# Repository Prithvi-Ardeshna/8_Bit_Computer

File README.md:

# 8-Bit Computer 

This project is a simulation of an 8-bit computer built using [Logisim Evolution](https://github.com/reds-heig/logisim-evolution), inspired by [Ben Eater's YouTube series](https://www.youtube.com/playlist?list=PLowKtXNTBypGqImE405J2565dvjafglHU).  
It demonstrates the basic architecture and functioning of a simple CPU, including a version with full control logic and basic instruction set support.

---

## Project Overview

This project includes **two versions** of the 8-bit CPU:

1. **Basic Version (without control logic):**  
   - Manually controlled CPU execution by execution micro instructions at a time.
   - Useful for learning how individual components interact.

2. **Full Version (with control logic):**  
   - Automated instruction execution using a control logic ROM.
   - Supports a simple assembly-like instruction set.

---

## Features

- Simulates an 8-bit CPU architecture.
- Includes ALU, Registers, RAM, Memory Address Register, Program Counter, Instruction Register, Flag Register, Control Logic, and Output Register.
- Simple instruction set to write and execute custom programs.
- C program to generate microcode that has to be loaded in control logic rom.

---

## Components

   **Clock**               

   **Program Counter**

   **A Register**        

   **B Register**     

   **ALU**             

   **Output Register**                       

   **Memory Address Register**               

   **RAM**                      

   **Instruction Register**         

   **Step Counter**                    

   **Zero Flag**                    

   **Flags**                         

---

## Instruction Set

| Opcode | Mnemonic | Description                     |
|--------|----------|---------------------------------|
| `0000` | NOP      | No operation                    |
| `0001` | LDA      | Load from RAM to A              |
| `0010` | ADD      | Add value to A                  |
| `0011` | SUB      | Subtract value from A           |
| `0100` | STA      | Store A to RAM                  |
| `0101` | LDI      | Load A with given value         |
| `0110` | JMP      | Jump to address                 |
| `0111` | JC       | Jump if carry flag is set       |
| `1000` | JZ       | Jump if zero flag is set        |
| `1110` | OUT      | Load from A to output register  |
| `1111` | HLT      | Halt execution                  |

---

## Examples

1) Using basic version to add two numbers

   Program:
   | Assembly | Memory Address | Machine Code |
   |----------|----------------|--------------|
   | LDA 14   | `0000`         | `0001 1110`  |
   | ADD 15   | `0001`         | `0010 1111`  |
   | OUT      | `0010`         | `1110 0000`  |
   |          |  ...           |              |
   |          | `1110`         | `0001 1100`  |
   |          | `1111`         | `0000 1110`  |

   Micro Instructions:

   |    | LDA 14 |                                                   | 
   |----|--------|---------------------------------------------------|
   | T0 | CO MI  | Going to Memory Address '0000' (Fetch opertation) |
   | T1 | RO II  | Transfer Data from RAM To IR                      |
   |    | CE     | Increment PC                                      |
   | T2 | IO MI  | Pointing Memory at address '1110'                 |
   | T3 | RO AI  | Store data in A                                   |

   |    | ADD 15 |                                                   | 
   |----|--------|---------------------------------------------------|
   | T0 | CO MI  | Going to Memory Address '0001' (Fetch opertation) |
   | T1 | RO II  | Transfer Data from RAM To IR                      |
   |    | CE     | Increment PC                                      |
   | T2 | IO MI  | Pointing Memory at address '1111'                 |
   | T3 | RO BI  | Store data in B                                   |
   | T4 | EO AI  | Calculate sum of A and B and store it in A        |

   |    | OUT    |                                                                  |
   |----|--------|------------------------------------------------------------------|
   | T0 | CO MI  | Going to Memory Address '0010' (Fetch opertation)                |
   | T1 | RO II  | Transfer Data from RAM To IR                                     |
   |    | CE     | Increment PC                                                     |
   | T2 | AO OI  | data stored in A is transfered to Output Register for displaying |

2) Getting Multiples of 3
   
   Program:
   | Assembly  | Memory Address | Machine Code |
   |-----------|----------------|--------------|
   | 0: LDI 03 | `0000`         | `0101 0011`  |
   | 1: STA 15 | `0001`         | `0100 1111`  |
   | 2: LDI 00 | `0010`         | `0101 0000`  |
   | 3: ADD 15 | `0011`         | `0010 1111`  |
   | 4: OUT    | `0100`         | `1110 0000`  |
   | 5: JMP 03 | `0101`         | `0110 0011`  |

3) Counting Up and Down

   Program:
   | Assembly   | Memory Address | Machine Code |
   |------------|----------------|--------------|
   | 00: OUT    | `0000`         | `1110 0000`  |
   | 01: ADD 15 | `0001`         | `0010 1111`  |
   | 02: JC 04  | `0010`         | `0111 0100`  |
   | 03: JMP 00 | `0011`         | `0110 0000`  |
   | 04: SUB 15 | `0100`         | `0011 1111`  |
   | 05: OUT    | `0101`         | `111O OOOO`  |
   | 06: JZ 00  | `0110`         | `1000 0000`  |
   | 07: JMP 04 | `0111`         | `0110 0100`  |
   | 15: 25     | `1111`         | `0011 0010`  |

4) Multipling x & y using conditional jump

   Pseudocode:\
   product = 0\
   loop until x is 0\
   &emsp;load x\
   &emsp;subtract 1\
   &emsp;store x\
   &emsp;load product\
   &emsp;add y\
   &emsp;store product\
   output product

   Assembly:\
   TOP:\
   &emsp;LDA x\
   &emsp;SUB 1\
   &emsp;JC CONTINUE\
   &emsp;LDA product\
   &emsp;OUT\
   &emsp;HLT\
   CONTINUE:\
   &emsp;STA x\
   &emsp;LDA product\
   &emsp;ADD y\
   &emsp;STA product\
   &emsp;JMP TOP

   Program:
   | Assembly    | Memory Address | Machine Code |
   |-------------|----------------|--------------|
   | 00: LDA 14  | `0000`         | `0001 1110`  |
   | 01: SUB 12  | `0001`         | `0011 1100`  |
   | 02: JC 06   | `0010`         | `0111 0110`  |
   | 03: LDA 13  | `0011`         | `0001 1101`  |
   | 04: OUT     | `0100`         | `1110 0000`  |
   | 05: HLT     | `0101`         | `1111 0000`  |
   | 06: STA 14  | `0110`         | `0100 1110`  |
   | 07: LDA 13  | `0111`         | `0001 1101`  |
   | 08: ADD 15  | `1000`         | `0010 1111`  |
   | 09: STA 13  | `1001`         | `0100 1101`  |
   | 10: JMP 00  | `1010`         | `0110 0000`  |
   | 11:         | `1011`         |              |
   | 12: 1       | `1100`         | `0000 0001`  |
   | 13: product | `1101`         | `0000 0000`  |
   | 14: x       | `1110`         |              |
   | 15: y       | `1111`         |              |

---

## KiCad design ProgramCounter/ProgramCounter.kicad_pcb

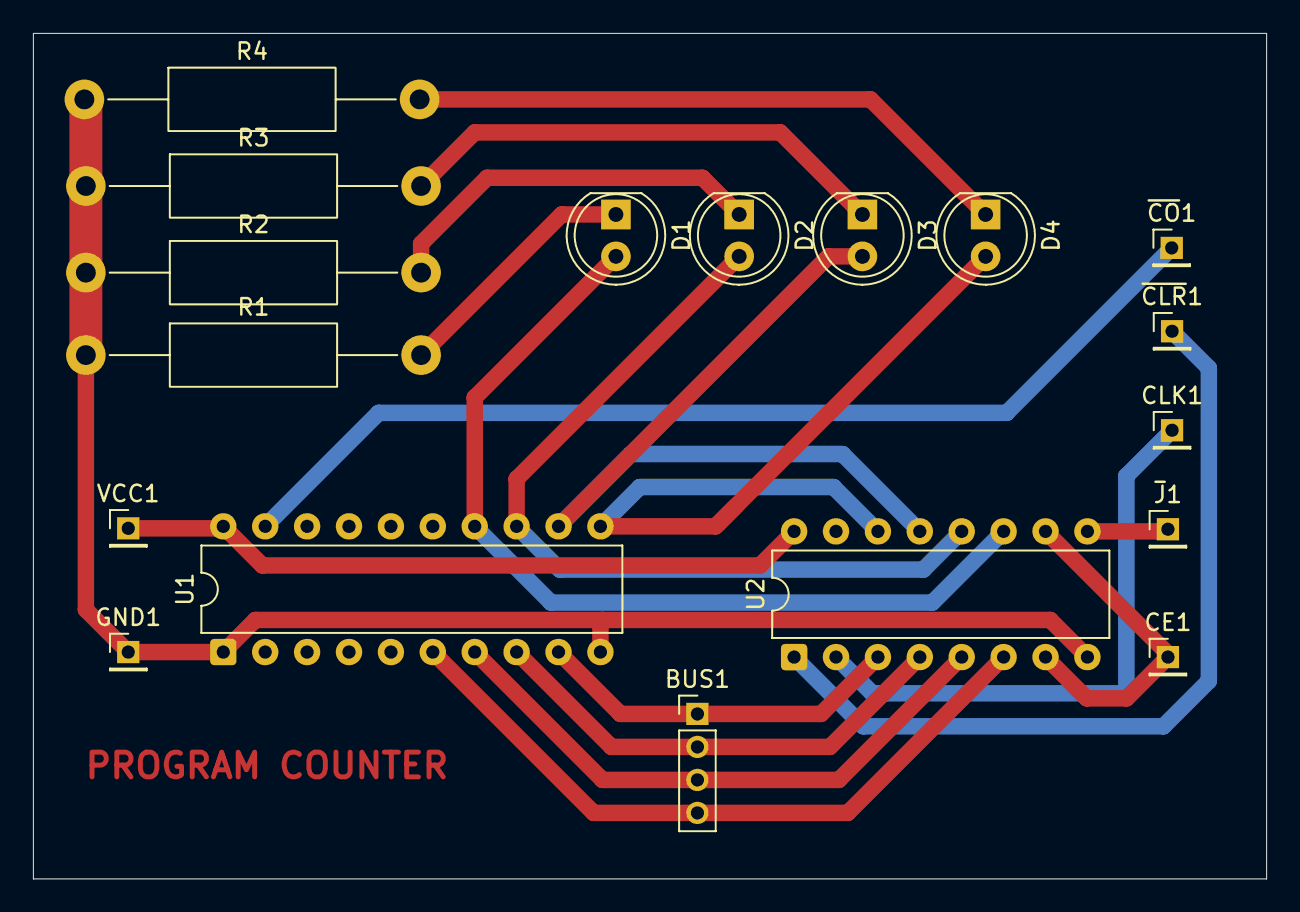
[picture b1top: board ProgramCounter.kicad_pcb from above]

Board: 2 copper layers, 74.8 x 51.2 mm, 15 parts (0 on the bottom side), 16 nets.

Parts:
BUS1: Conn_01x04_Pin; PinHeader_1x04_P2.00mm_Vertical
CE1: Conn_01x01_Pin; PinHeader_1x01_P2.00mm_Vertical
CLK1: Conn_01x01_Pin; PinHeader_1x01_P2.00mm_Vertical
D1, D2, D3, D4: LED; LED_D5.0mm
GND1: Conn_01x01_Pin; PinHeader_1x01_P2.00mm_Vertical
R1, R2, R3, R4: R; R_Axial_DIN0411_L9.9mm_D3.6mm_P20.32mm_Horizontal
U1: 74LS245; DIP-20_W7.62mm
U2: 74LS161; DIP-16_W7.62mm
VCC1: Conn_01x01_Pin; PinHeader_1x01_P2.00mm_Vertical

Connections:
unnamed: BUS1.1, U1.9 (A7), U2.3 (D0)
unnamed: BUS1.2, U1.8 (A6), U2.4 (D1)
unnamed: BUS1.3, U1.7 (A5), U2.5 (D2)
unnamed: BUS1.4, U1.6 (A4), U2.6 (D3)
unnamed: CE1.1, U2.7 (CEP), U2.10 (CET)
unnamed: CLK1.1, U2.2 (CP)
unnamed: D1.2 (A), U1.14 (B4), U2.11 (Q3)
unnamed: D1.1 (K), R1.2
unnamed: D2.2 (A), U1.13 (B5), U2.12 (Q2)
unnamed: D2.1 (K), R2.2
unnamed: D3.2 (A), U1.12 (B6), U2.13 (Q1)
unnamed: D3.1 (K), R3.2
unnamed: D4.2 (A), U1.11 (B7), U2.14 (Q0)
unnamed: D4.1 (K), R4.2
unnamed: GND1.1, R1.1, R2.1, R3.1, R4.1, U1.1 (A->B), U1.10 (GND), U2.8 (GND)
unnamed: U1.20 (VCC), U2.16 (VCC), VCC1.1

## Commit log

2025-07-24 Create README.md v1
2026-03-12 Update instruction in README for clarity
